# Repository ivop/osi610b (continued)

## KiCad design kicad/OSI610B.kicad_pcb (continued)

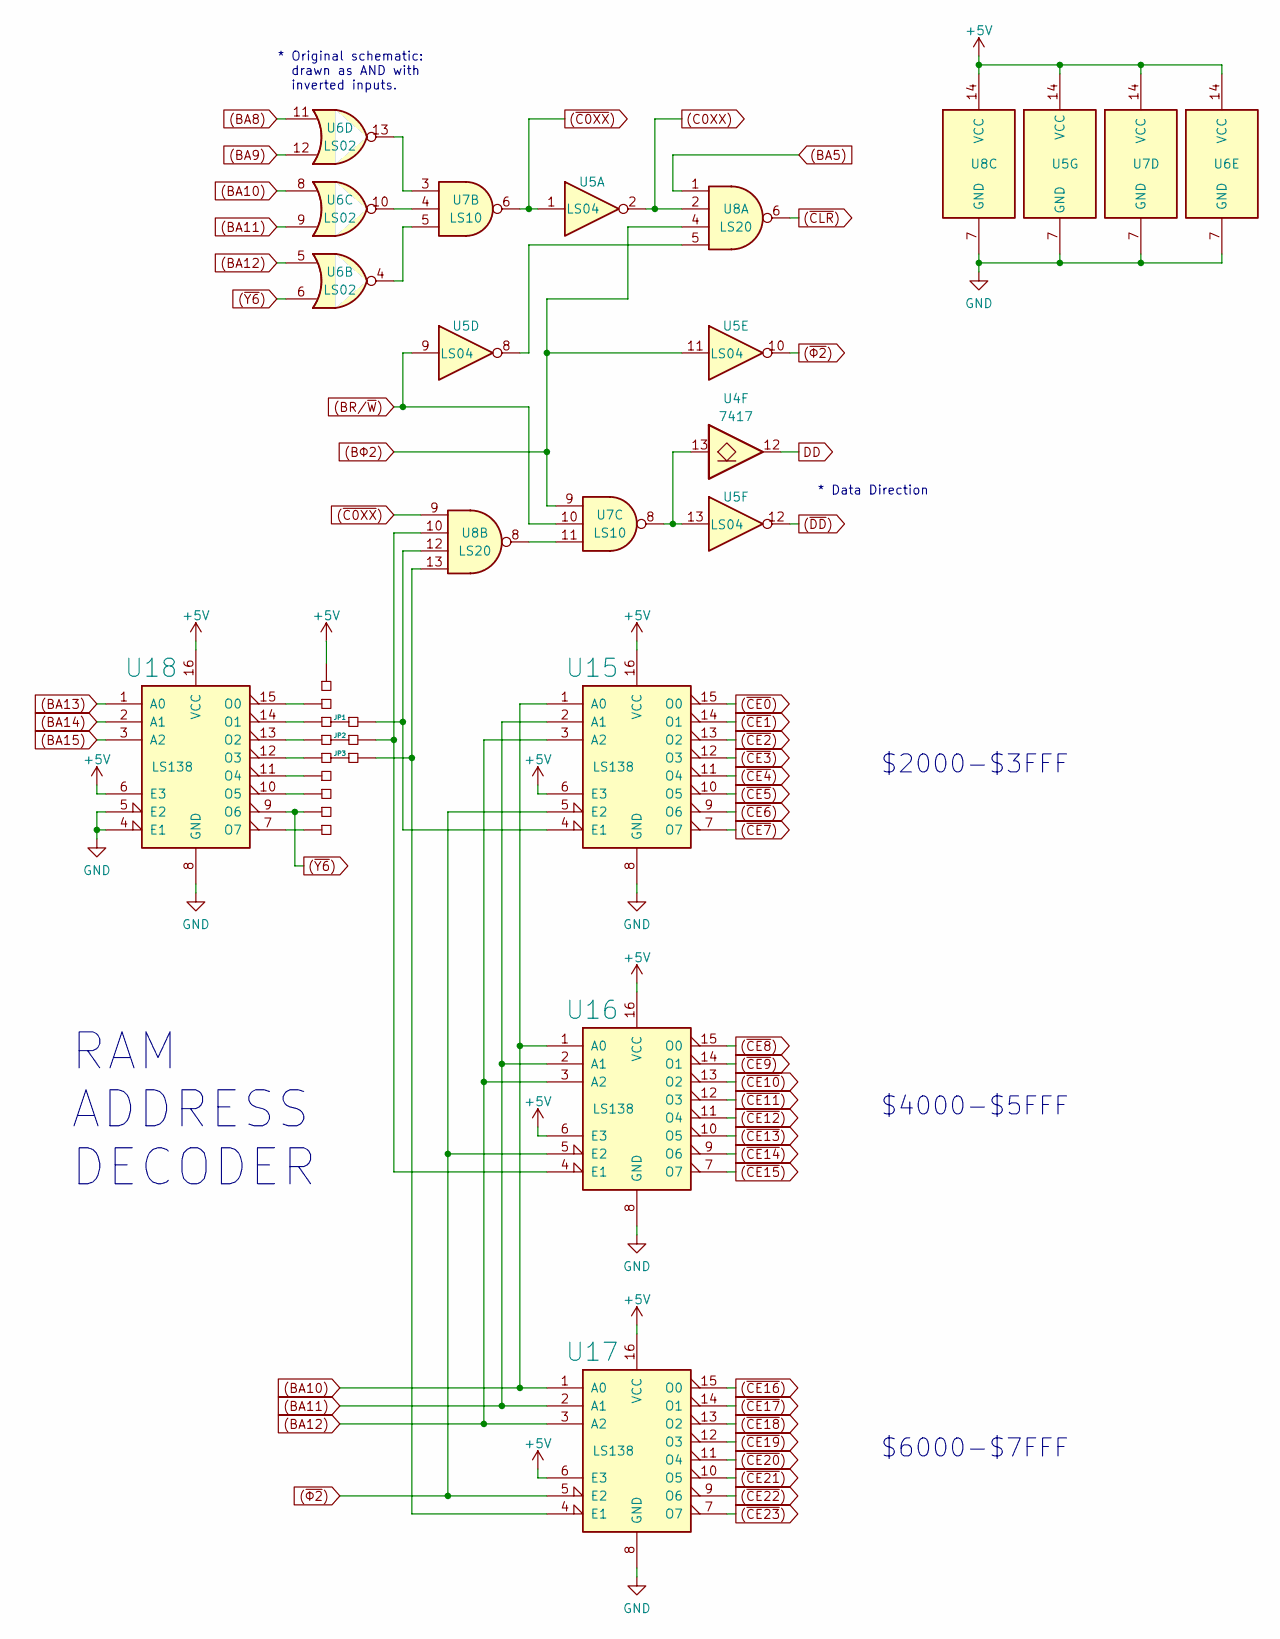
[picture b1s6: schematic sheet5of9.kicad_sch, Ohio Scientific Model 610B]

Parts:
JP1, JP2, JP3: JUMPER_BRIDGED_12; Closed PinHeader_1x02_P2.54mm_Vertical
PIN6: 2PINS; PinHeader_1x02_P2.54mm_Vertical
PIN7: 4PINS; PinHeader_1x04_P2.54mm_Vertical
U4: 7417; DIP-14_W7.62mm_Socket_LongPads
U5: LS04; DIP-14_W7.62mm_Socket_LongPads
U6: LS02; DIP-14_W7.62mm_Socket_LongPads
U7: LS10; DIP-14_W7.62mm_Socket_LongPads
U8: LS20; DIP-14_W7.62mm_Socket_LongPads
U15, U16, U17, U18: LS138; DIP-16_W7.62mm_Socket_LongPads

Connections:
(BA5): U8.1; also elsewhere on the board
(BA8): U6.11; also elsewhere on the board
(BA9): U6.12; also elsewhere on the board
(BA10): U6.8, U15.1 (A0), U16.1 (A0), U17.1 (A0); also elsewhere on the board
(BA11): U6.9, U15.2 (A1), U16.2 (A1), U17.2 (A1); also elsewhere on the board
(BA12): U6.5, U15.3 (A2), U16.3 (A2), U17.3 (A2); also elsewhere on the board
(BA13): U18.1 (A0); also elsewhere on the board
(BA14): U18.2 (A1); also elsewhere on the board
(BA15): U18.3 (A2); also elsewhere on the board
(BR/~W): U5.9, U7.10; also elsewhere on the board
(BΦ2): U5.11, U7.9, U8.4; also elsewhere on the board
(C0XX): U5.2, U8.2; also elsewhere on the board
(~C0XX): U5.1, U7.6, U8.9; also elsewhere on the board
(~CE0): U15.15 (O0); also elsewhere on the board
(~CE1): U15.14 (O1); also elsewhere on the board
(~CE2): U15.13 (O2); also elsewhere on the board
(~CE3): U15.12 (O3); also elsewhere on the board
(~CE4): U15.11 (O4); also elsewhere on the board
(~CE5): U15.10 (O5); also elsewhere on the board
(~CE6): U15.9 (O6); also elsewhere on the board
(~CE7): U15.7 (O7); also elsewhere on the board
(~CE8): U16.15 (O0); also elsewhere on the board
(~CE9): U16.14 (O1); also elsewhere on the board
(~CE10): U16.13 (O2); also elsewhere on the board
(~CE11): U16.12 (O3); also elsewhere on the board
(~CE12): U16.11 (O4); also elsewhere on the board
(~CE13): U16.10 (O5); also elsewhere on the board
(~CE14): U16.9 (O6); also elsewhere on the board
(~CE15): U16.7 (O7); also elsewhere on the board
(~CE16): U17.15 (O0); also elsewhere on the board
(~CE17): U17.14 (O1); also elsewhere on the board
(~CE18): U17.13 (O2); also elsewhere on the board
(~CE19): U17.12 (O3); also elsewhere on the board
(~CE20): U17.11 (O4); also elsewhere on the board
(~CE21): U17.10 (O5); also elsewhere on the board
(~CE22): U17.9 (O6); also elsewhere on the board
(~CE23): U17.7 (O7); also elsewhere on the board
(~CLR): U8.6; also elsewhere on the board
(~DD): U5.12; also elsewhere on the board
(~Y6): PIN7.3, U6.6, U18.9 (O6)
(~Φ2): U5.10, U15.5 (E2), U16.5 (E2), U17.5 (E2); also elsewhere on the board
+5V: PIN6.1, U5.14 (VCC), U6.14 (VCC), U7.14 (VCC), U8.14 (VCC), U15.6 (E3), U15.16 (VCC), U16.6 (E3), U16.16 (VCC), U17.6 (E3), U17.16 (VCC), U18.6 (E3), U18.16 (VCC); also elsewhere on the board
DD: U4.12 (6Y); also elsewhere on the board
GND: U5.7 (GND), U6.7 (GND), U7.7 (GND), U8.7 (GND), U15.8 (GND), U16.8 (GND), U17.8 (GND), U18.4 (E1), U18.5 (E2), U18.8 (GND); also elsewhere on the board
unnamed: JP1.1, U18.14 (O1)
unnamed: JP1.2, U8.12, U15.4 (E1)
unnamed: JP2.1, U18.13 (O2)
unnamed: JP2.2, U8.10, U16.4 (E1)
unnamed: JP3.1, U18.12 (O3)
unnamed: JP3.2, U8.13, U17.4 (E1)
unnamed: PIN6.2, U18.15 (O0)
unnamed: PIN7.1, U18.11 (O4)
unnamed: PIN7.2, U18.10 (O5)
unnamed: PIN7.4, U18.7 (O7)
unnamed: U4.13 (6A), U5.13, U7.8
unnamed: U5.8, U8.5
unnamed: U6.4, U7.5
unnamed: U6.10, U7.4
unnamed: U6.13, U7.3
unnamed: U7.11, U8.8

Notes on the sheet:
$6000-$7FFF
$2000-$3FFF
* Original schematic: drawn as AND with inverted inputs.
$4000-$5FFF
RAM ADDRESS DECODER
* Data Direction

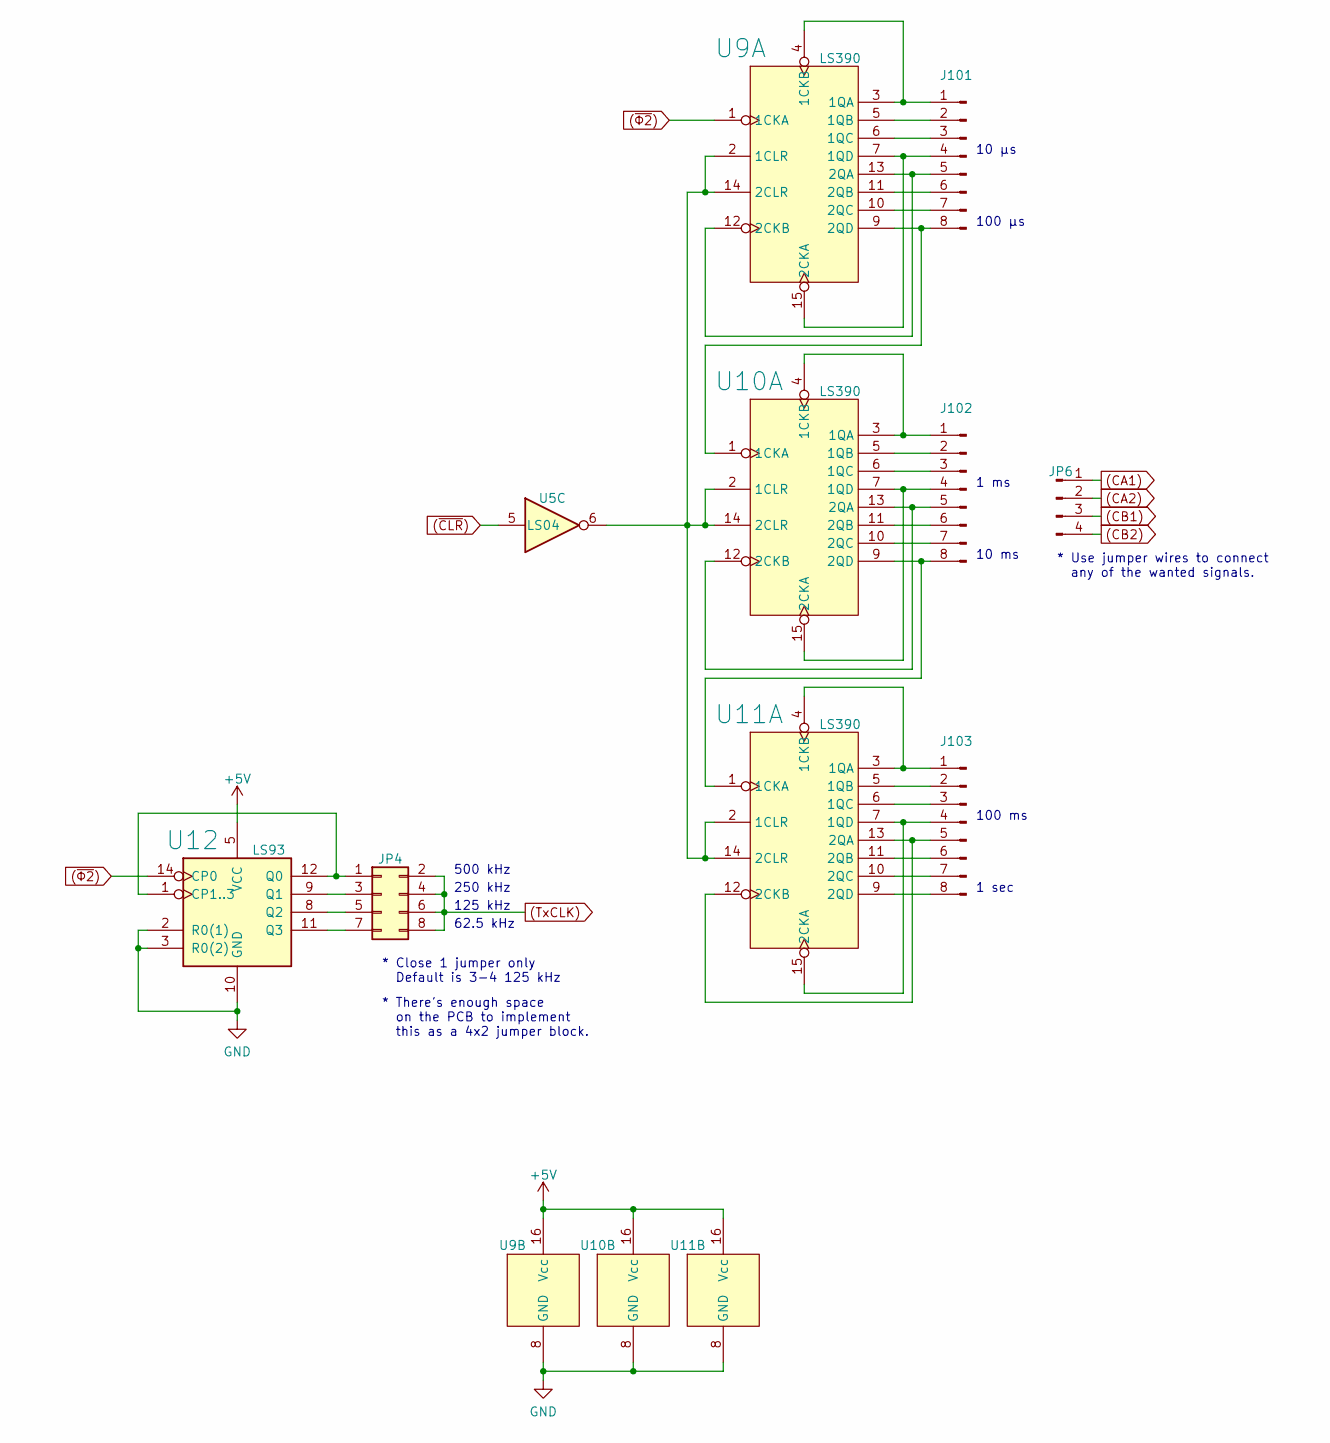
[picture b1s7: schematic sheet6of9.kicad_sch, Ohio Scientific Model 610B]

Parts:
J101, J102, J103: Conn_01x08_Male; PinHeader_1x08_P2.54mm_Vertical
JP4: Conn_02x04_Odd_Even; JP4 Closed PinHeader_2x04_P2.54mm_Vertical
JP6: Conn_01x04_Male; PinHeader_1x04_P2.54mm_Vertical
U5: LS04; DIP-14_W7.62mm_Socket_LongPads
U9, U10, U11: LS390; DIP-16_W7.62mm_Socket_LongPads
U12: LS93; DIP-14_W7.62mm_Socket_LongPads

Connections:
(CA1): JP6.1; also elsewhere on the board
(CA2): JP6.2; also elsewhere on the board
(CB1): JP6.3; also elsewhere on the board
(CB2): JP6.4; also elsewhere on the board
(TxCLK): JP4.2, JP4.4, JP4.6, JP4.8; also elsewhere on the board
(~CLR): U5.5; also elsewhere on the board
(~Φ2): U9.1 (1CKA), U12.14 (CP0); also elsewhere on the board
+5V: U9.16 (Vcc), U10.16 (Vcc), U11.16 (Vcc), U12.5 (VCC); also elsewhere on the board
GND: U9.8 (GND), U10.8 (GND), U11.8 (GND), U12.2 (R0(1)), U12.3 (R0(2)), U12.10 (GND); also elsewhere on the board
unnamed: J101.1, U9.3 (1QA), U9.4 (1CKB)
unnamed: J101.2, U9.5 (1QB)
unnamed: J101.3, U9.6 (1QC)
unnamed: J101.4, U9.7 (1QD), U9.15 (2CKA)
unnamed: J101.5, U9.12 (2CKB), U9.13 (2QA)
unnamed: J101.6, U9.11 (2QB)
unnamed: J101.7, U9.10 (2QC)
unnamed: J101.8, U9.9 (2QD), U10.1 (1CKA)
unnamed: J102.1, U10.3 (1QA), U10.4 (1CKB)
unnamed: J102.2, U10.5 (1QB)
unnamed: J102.3, U10.6 (1QC)
unnamed: J102.4, U10.7 (1QD), U10.15 (2CKA)
unnamed: J102.5, U10.12 (2CKB), U10.13 (2QA)
unnamed: J102.6, U10.11 (2QB)
unnamed: J102.7, U10.10 (2QC)
unnamed: J102.8, U10.9 (2QD), U11.1 (1CKA)
unnamed: J103.1, U11.3 (1QA), U11.4 (1CKB)
unnamed: J103.2, U11.5 (1QB)
unnamed: J103.3, U11.6 (1QC)
unnamed: J103.4, U11.7 (1QD), U11.15 (2CKA)
unnamed: J103.5, U11.12 (2CKB), U11.13 (2QA)
unnamed: J103.6, U11.11 (2QB)
unnamed: J103.7, U11.10 (2QC)
unnamed: J103.8, U11.9 (2QD)
unnamed: JP4.1, U12.1 (CP1..3), U12.12 (Q0)
unnamed: JP4.3, U12.9 (Q1)
unnamed: JP4.5, U12.8 (Q2)
unnamed: JP4.7, U12.11 (Q3)
unnamed: U5.6, U9.2 (1CLR), U9.14 (2CLR), U10.2 (1CLR), U10.14 (2CLR), U11.2 (1CLR), U11.14 (2CLR)

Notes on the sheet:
* Close 1 jumper only Default is 3-4 125 kHz
* There's enough space on the PCB to implement this as a 4x2 jumper block.
1 sec
100 ms
500 kHz
62.5 kHz
10 ms
1 ms
125 kHz
* Use jumper wires to connect any of the wanted signals.
100 μs
10 μs
250 kHz

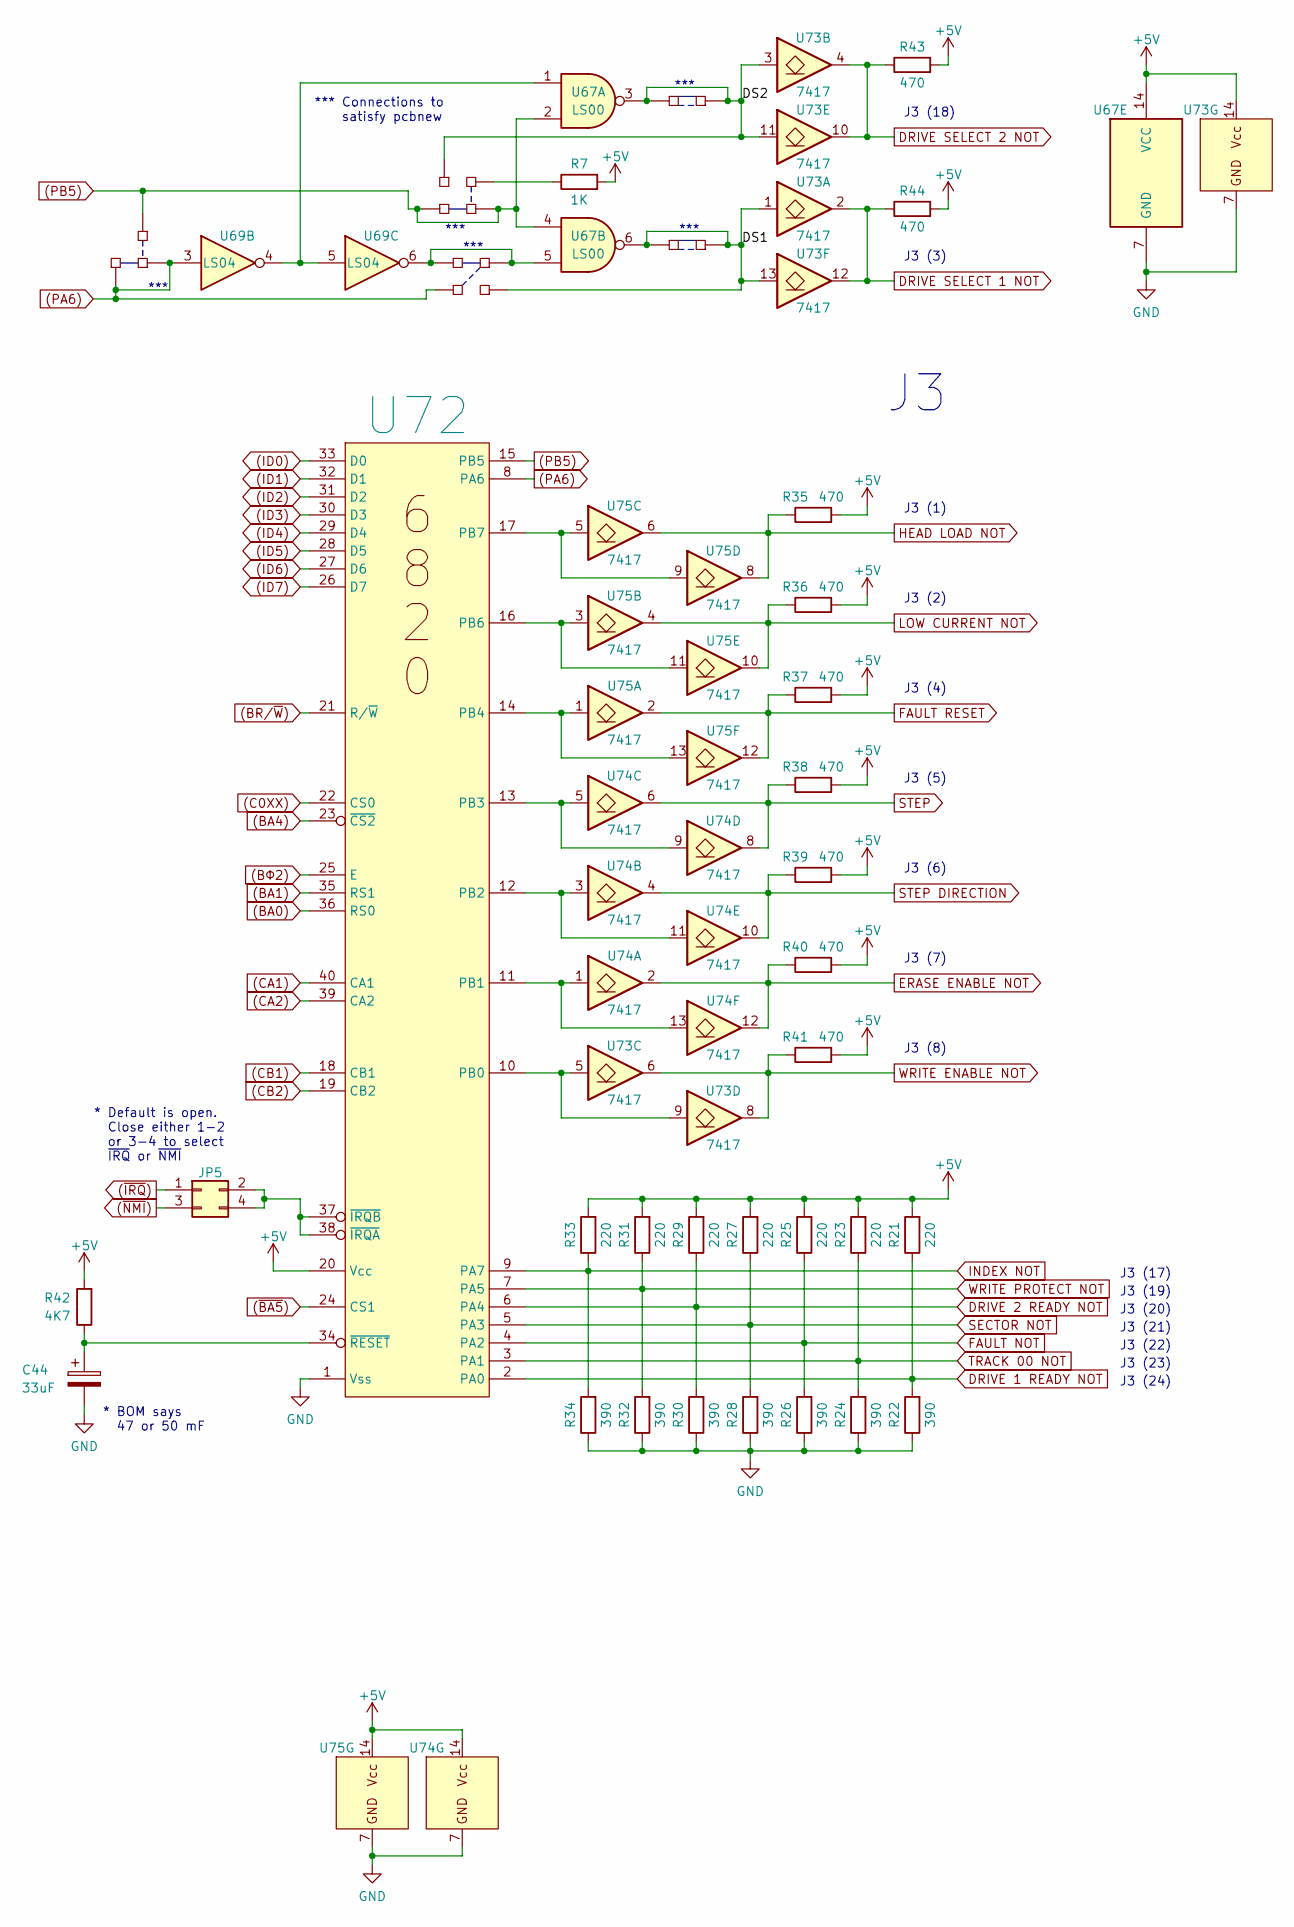
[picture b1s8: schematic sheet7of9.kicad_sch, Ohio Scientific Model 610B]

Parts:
C44: 33uF; CP_Axial_L11.0mm_D6.0mm_P18.00mm_Horizontal
JP5: Conn_02x02_Odd_Even; PinHeader_2x02_P2.54mm_Vertical
PIN11, PIN12, PIN13, PIN14, PIN15, PIN16, PIN17, PIN18, PIN19, PIN20, PIN21, PIN22, PIN23, PIN24, PIN25: PIN; No Silkscreen PinHeader_1x01_P2.54mm_Vertical
R7: 1K; R_Axial_DIN0309_L9.0mm_D3.2mm_P12.70mm_Horizontal
R21, R23, R25, R27, R29, R31, R33: 220; R_Axial_DIN0309_L9.0mm_D3.2mm_P12.70mm_Horizontal
R22, R24, R26, R28, R30, R32, R34: 390; R_Axial_DIN0309_L9.0mm_D3.2mm_P12.70mm_Horizontal
R35, R36, R37, R38, R39, R40, R41, R43, R44: 470; R_Axial_DIN0309_L9.0mm_D3.2mm_P12.70mm_Horizontal
R42: 4K7; R_Axial_DIN0309_L9.0mm_D3.2mm_P12.70mm_Horizontal
U67: LS00; DIP-14_W7.62mm_Socket_LongPads
U69: LS04; DIP-14_W7.62mm_Socket_LongPads
U72: 6820; DIP-40_W15.24mm_Socket_LongPads
U73, U74, U75: 7417; DIP-14_W7.62mm_Socket_LongPads

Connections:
(BA0): U72.36 (RS0); also elsewhere on the board
(BA1): U72.35 (RS1); also elsewhere on the board
(BA4): U72.23 (~CS2); also elsewhere on the board
(BR/~W): U72.21 (R/~W); also elsewhere on the board
(BΦ2): U72.25 (E); also elsewhere on the board
(C0XX): U72.22 (CS0); also elsewhere on the board
(CA1): U72.40 (CA1); also elsewhere on the board
(CA2): U72.39 (CA2); also elsewhere on the board
(CB1): U72.18 (CB1); also elsewhere on the board
(CB2): U72.19 (CB2); also elsewhere on the board
(ID0): U72.33 (D0); also elsewhere on the board
(ID1): U72.32 (D1); also elsewhere on the board
(ID2): U72.31 (D2); also elsewhere on the board
(ID3): U72.30 (D3); also elsewhere on the board
(ID4): U72.29 (D4); also elsewhere on the board
(ID5): U72.28 (D5); also elsewhere on the board
(ID6): U72.27 (D6); also elsewhere on the board
(ID7): U72.26 (D7); also elsewhere on the board
(PA6): PIN12.1, PIN13.1, PIN20.1, U69.3, U72.8 (PA6)
(PB5): PIN11.1, PIN16.1, PIN17.1, U67.2, U67.4, U72.15 (PB5)
(~BA5): U72.24 (CS1); also elsewhere on the board
(~IRQ): JP5.1; also elsewhere on the board
(~NMI): JP5.3; also elsewhere on the board
+5V: R7.2, R21.2, R23.2, R25.2, R27.2, R29.2, R31.2, R33.2, R35.2, R36.2, R37.2, R38.2, R39.2, R40.2, R41.2, R42.2, R43.2, R44.2, U67.14 (VCC), U72.20 (Vcc), U73.14 (Vcc), U74.14 (Vcc), U75.14 (Vcc); also elsewhere on the board
/SHEET SEVEN OF NINE/DS1: PIN21.1, PIN24.1, PIN25.1, U67.6, U73.1 (1A), U73.13 (6A)
/SHEET SEVEN OF NINE/DS2: PIN14.1, PIN22.1, PIN23.1, U67.3, U73.3 (3A), U73.11 (5A)
DRIVE 1 READY NOT: R21.1, R22.2, U72.2 (PA0); also elsewhere on the board
DRIVE 2 READY NOT: R29.1, R30.2, U72.6 (PA4); also elsewhere on the board
DRIVE SELECT 1 NOT: R44.1, U73.2 (1Y), U73.12 (6Y); also elsewhere on the board
DRIVE SELECT 2 NOT: R43.1, U73.4 (3Y), U73.10 (5Y); also elsewhere on the board
ERASE ENABLE NOT: R40.1, U74.2 (1Y), U74.12 (6Y); also elsewhere on the board
FAULT NOT: R25.1, R26.2, U72.4 (PA2); also elsewhere on the board
FAULT RESET: R37.1, U75.2 (1Y), U75.12 (6Y); also elsewhere on the board
GND: C44.2, R22.1, R24.1, R26.1, R28.1, R30.1, R32.1, R34.1, U67.7 (GND), U72.1 (Vss), U73.7 (GND), U74.7 (GND), U75.7 (GND); also elsewhere on the board
HEAD LOAD NOT: R35.1, U75.6 (3Y), U75.8 (4Y); also elsewhere on the board
INDEX NOT: R33.1, R34.2, U72.9 (PA7); also elsewhere on the board
LOW CURRENT NOT: R36.1, U75.4 (3Y), U75.10 (5Y); also elsewhere on the board
unnamed 114: C44.1, R42.1, U72.34 (~RESET); also elsewhere on the board
unnamed: JP5.2, JP5.4, U72.37 (~IRQB), U72.38 (~IRQA)
unnamed: PIN15.1, R7.1
unnamed: PIN18.1, PIN19.1, U67.5, U69.6
unnamed: U67.1, U69.4, U69.5
unnamed: U72.10 (PB0), U73.5 (3A), U73.9 (4A)
unnamed: U72.11 (PB1), U74.1 (1A), U74.13 (6A)
unnamed: U72.12 (PB2), U74.3 (3A), U74.11 (5A)
unnamed: U72.13 (PB3), U74.5 (3A), U74.9 (4A)
unnamed: U72.14 (PB4), U75.1 (1A), U75.13 (6A)
unnamed: U72.16 (PB6), U75.3 (3A), U75.11 (5A)
unnamed: U72.17 (PB7), U75.5 (3A), U75.9 (4A)
SECTOR NOT: R27.1, R28.2, U72.5 (PA3); also elsewhere on the board
STEP: R38.1, U74.6 (3Y), U74.8 (4Y); also elsewhere on the board
STEP DIRECTION: R39.1, U74.4 (3Y), U74.10 (5Y); also elsewhere on the board
TRACK 00 NOT: R23.1, R24.2, U72.3 (PA1); also elsewhere on the board
WRITE ENABLE NOT: R41.1, U73.6 (3Y), U73.8 (4Y); also elsewhere on the board
WRITE PROTECT NOT: R31.1, R32.2, U72.7 (PA5); also elsewhere on the board

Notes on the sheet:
J3 (20)
*** Connections to satisfy pcbnew
***
* BOM says 47 or 50 mF
J3 (22)
J3 (7)
* Default is open. Close either 1-2 or 3-4 to select ~{IRQ} or ~{NMI}
J3 (24)
J3 (4)
J3 (1)
J3 (17)
J3 (8)
J3 (6)
J3 (2)
J3 (3)
J3 (19)
J3 (18)
J3 (23)
J3 (5)
J3 (21)

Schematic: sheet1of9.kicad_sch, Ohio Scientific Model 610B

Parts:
J1, J2: Conn_01x40_Male; DIP-40_W15.24mm_Socket_LongPads
PIN30: PIN; PinHeader_1x01_P2.54mm_Vertical
R1, R2, R3: 220; R_Axial_DIN0309_L9.0mm_D3.2mm_P12.70mm_Horizontal
R4, R5, R6: 390; R_Axial_DIN0309_L9.0mm_D3.2mm_P12.70mm_Horizontal
U1, U2, U3: 8T95; DIP-16_W7.62mm_Socket_LongPads
U4: 7417; DIP-14_W7.62mm_Socket_LongPads
U13, U14: 8T28; DIP-16_W7.62mm_Socket_LongPads
U69: LS04; DIP-14_W7.62mm_Socket_LongPads

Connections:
(BA0): J2.1, U1.5 (Y2); also elsewhere on the board
(BA1): J2.2, U1.13 (Y6); also elsewhere on the board
(BA2): J2.3, U1.3 (Y1); also elsewhere on the board
(BA3): J2.4, U1.11 (Y5); also elsewhere on the board
(BA4): J2.5, U1.7 (Y3); also elsewhere on the board
(BA5): J2.6, U1.9 (Y4), U69.11; also elsewhere on the board
(BA6): J2.7, U2.5 (Y2); also elsewhere on the board
(BA7): J2.8, U2.11 (Y5); also elsewhere on the board
(BA8): J2.33, U2.7 (Y3); also elsewhere on the board
(BA9): J2.34, U3.7 (Y3); also elsewhere on the board
(BA10): J2.35, U3.9 (Y4); also elsewhere on the board
(BA11): J2.36, U3.11 (Y5); also elsewhere on the board
(BA12): J2.37, U3.5 (Y2); also elsewhere on the board
(BA13): J2.38, U3.3 (Y1); also elsewhere on the board
(BA14): J2.39, U3.13 (Y6); also elsewhere on the board
(BA15): J2.40, U2.9 (Y4); also elsewhere on the board
(BR/~W): J2.15, U2.13 (Y6); also elsewhere on the board
(BΦ2): J2.19, U2.3 (Y1); also elsewhere on the board
(ID0): U13.2 (R0), U13.4 (D0); also elsewhere on the board
(ID1): U13.12 (D3), U13.14 (R3); also elsewhere on the board
(ID2): U13.5 (R1), U13.7 (D1); also elsewhere on the board
(ID3): U13.9 (D2), U13.11 (R2); also elsewhere on the board
(ID4): U14.2 (R0), U14.4 (D0); also elsewhere on the board
(ID5): U14.12 (D3), U14.14 (R3); also elsewhere on the board
(ID6): U14.5 (R1), U14.7 (D1); also elsewhere on the board
(ID7): U14.9 (D2), U14.11 (R2); also elsewhere on the board
(~BA5): U69.10; also elsewhere on the board
(~DD): U13.1 (RE), U13.15 (BE), U14.1 (RE), U14.15 (BE); also elsewhere on the board
(~IRQ): J1.1, U4.6 (3Y); also elsewhere on the board
(~NMI): J1.2, U4.4 (3Y); also elsewhere on the board
+5V: R1.1, R2.1, R3.1, U1.16 (Vcc), U2.16 (Vcc), U3.16 (Vcc), U4.14 (Vcc), U13.16 (Vcc), U14.16 (Vcc); also elsewhere on the board
A0: J1.14, U1.4 (I2)
A1: J1.13, U1.14 (I6)
A2: J1.12, U1.2 (I1)
A3: J1.15, U1.12 (I5)
A4: J1.16, U1.6 (I3)
A5: J1.17, U1.10 (I4)
A6: J1.18, U2.4 (I2)
A7: J1.19, U2.12 (I5)
A8: J1.20, U2.6 (I3)
A9: J1.21, U3.6 (I3)
A10: J1.22, U3.10 (I4)
A11: J1.23, U3.12 (I5)
A12: J1.24, U3.4 (I2)
A13: J1.25, U3.2 (I1)
A14: J1.26, U3.14 (I6)
A15: J1.27, U2.10 (I4)
BD0: J1.4, J2.10, U13.3 (B0)
BD1: J1.5, J2.11, U13.13 (B3)
BD2: J1.6, J2.12, U13.6 (B1)
BD3: J1.7, J2.13, U13.10 (B2)
BD4: J1.36, J2.28, U14.3 (B0)
BD5: J1.35, J2.29, U14.13 (B3)
BD6: J1.34, J2.30, U14.6 (B1)
BD7: J1.33, J2.31, U14.10 (B2)
BDD: J2.18, R3.2, R6.1, U4.1 (1A)
DD: J1.3, U4.2 (1Y); also elsewhere on the board
GND: J1.8, J1.9, J1.10, J1.28, J1.29, J1.30, J1.37, J1.38, J1.39, J1.40, J2.9, J2.14, J2.21, J2.22, J2.23, J2.24, J2.25, J2.26, J2.27, J2.32, R4.2, R5.2, R6.2, U1.1 (DIS1), U1.8 (GND), U1.15 (DIS2), U2.1 (DIS1), U2.8 (GND), U2.15 (DIS2), U3.1 (DIS1), U3.8 (GND), U3.15 (DIS2), U4.7 (GND), U13.8 (GND), U14.8 (GND); also elsewhere on the board
unnamed: J2.20, PIN30.1
R/~W: J1.32, U2.14 (I6)
~BIRQ: J2.16, R1.2, R4.1, U4.5 (3A)
~BNMI: J2.17, R2.2, R5.1, U4.3 (3A)
Φ2: J1.31, U2.2 (I1)

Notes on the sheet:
* Note that the original schematic had the 8T28 pins all messed up. Wrong order, and wrong names.
* GND is not on the original schematic, but it is on the PCB. Pin 20 is only connected to a via going nowhere.
* These connections are not on the original schematic, but the PCB ties them to GND

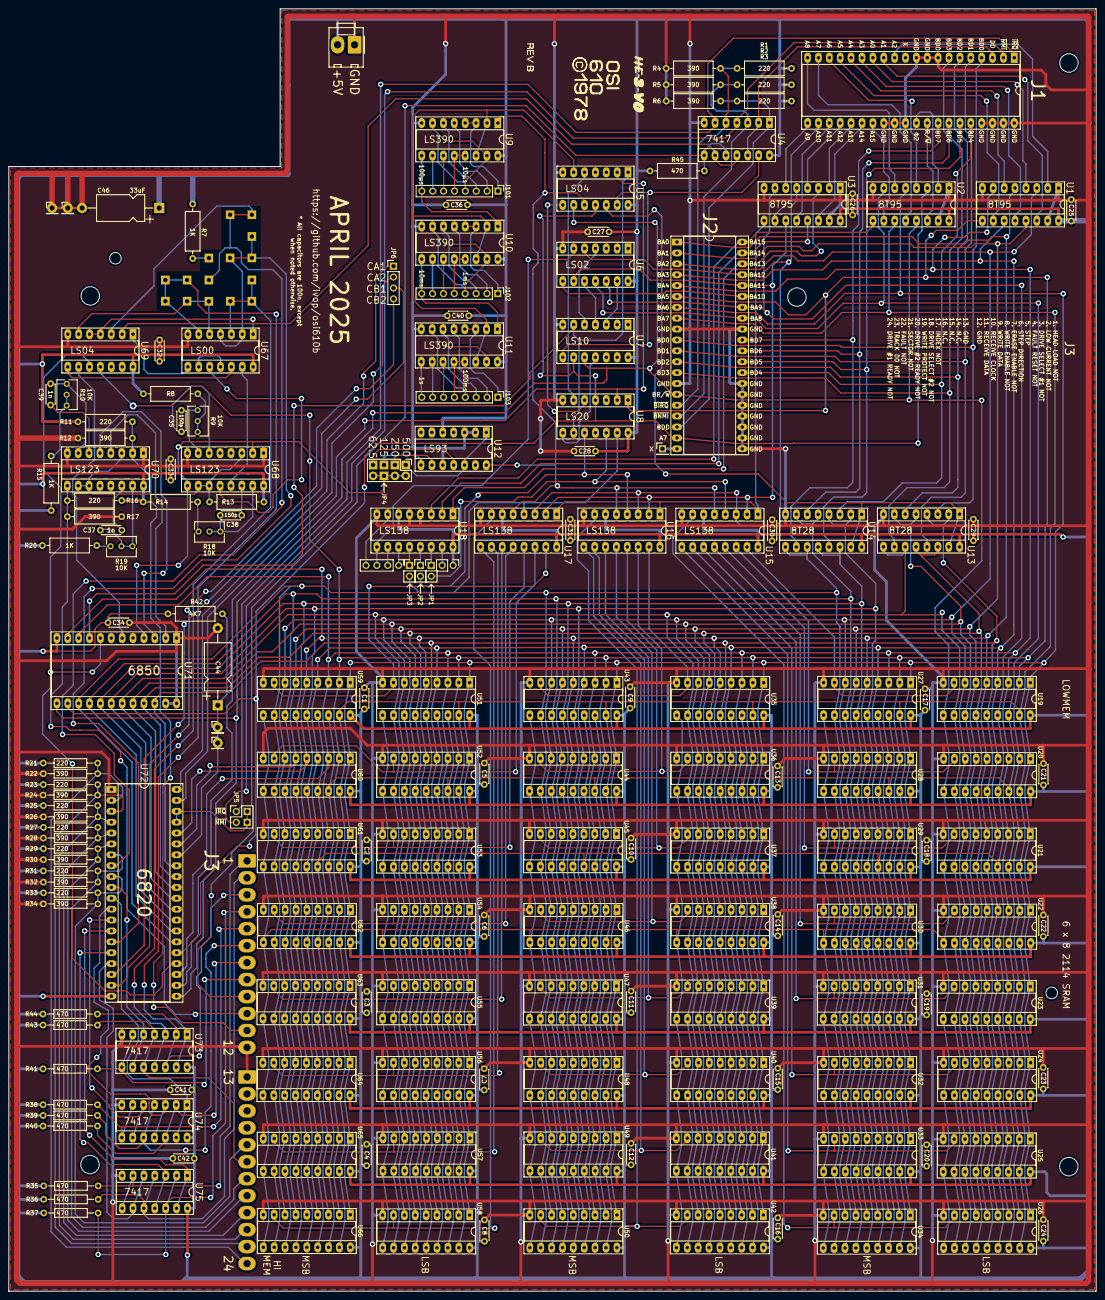
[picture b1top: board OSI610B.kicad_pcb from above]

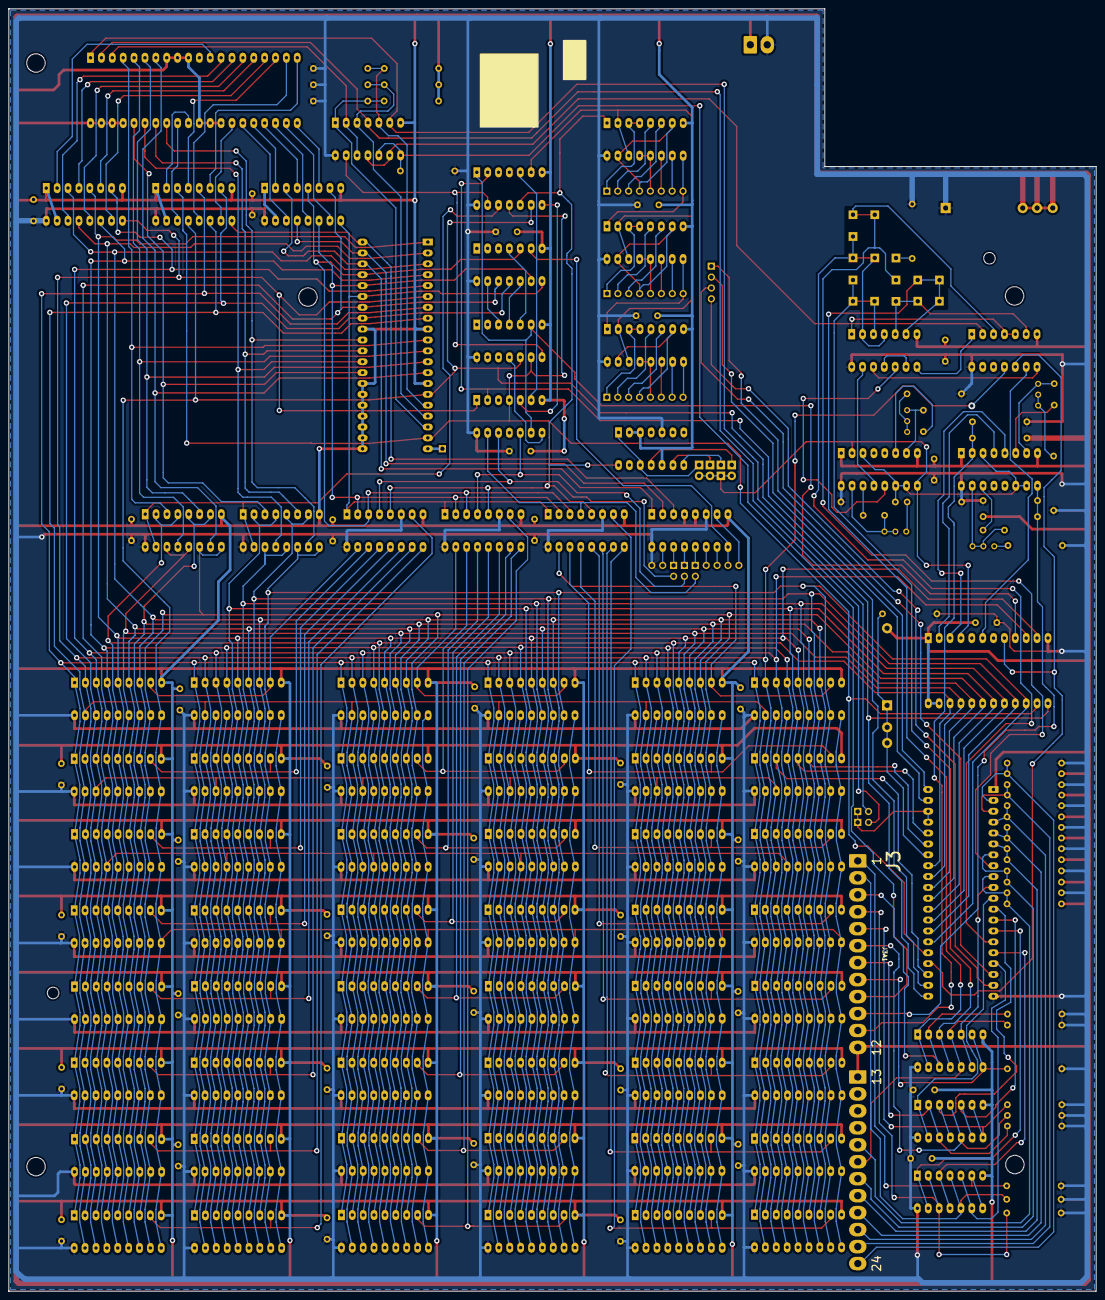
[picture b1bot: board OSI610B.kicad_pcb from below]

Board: 2 copper layers, 253.8 x 299.4 mm, 207 parts (2 on the bottom side), 199 nets.

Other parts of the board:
nis1, nis2, nis3, nis3#2: PinHeader_1x01_P2.54mm_Vertical

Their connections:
GND: nis1.1, nis2.1; also elsewhere on the board
unnamed 114: nis3.1, nis3#2.1; also elsewhere on the board

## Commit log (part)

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2025-04-29 First commit.
2025-04-30 Rename J3 signals. Update silkscreen with J3 signals legend. Add power connector.
2025-04-30 Add power connector 3D model.
2025-05-01 Fix mounting hole positions
2025-05-08 Switch J1 and J2 to pin headers.
